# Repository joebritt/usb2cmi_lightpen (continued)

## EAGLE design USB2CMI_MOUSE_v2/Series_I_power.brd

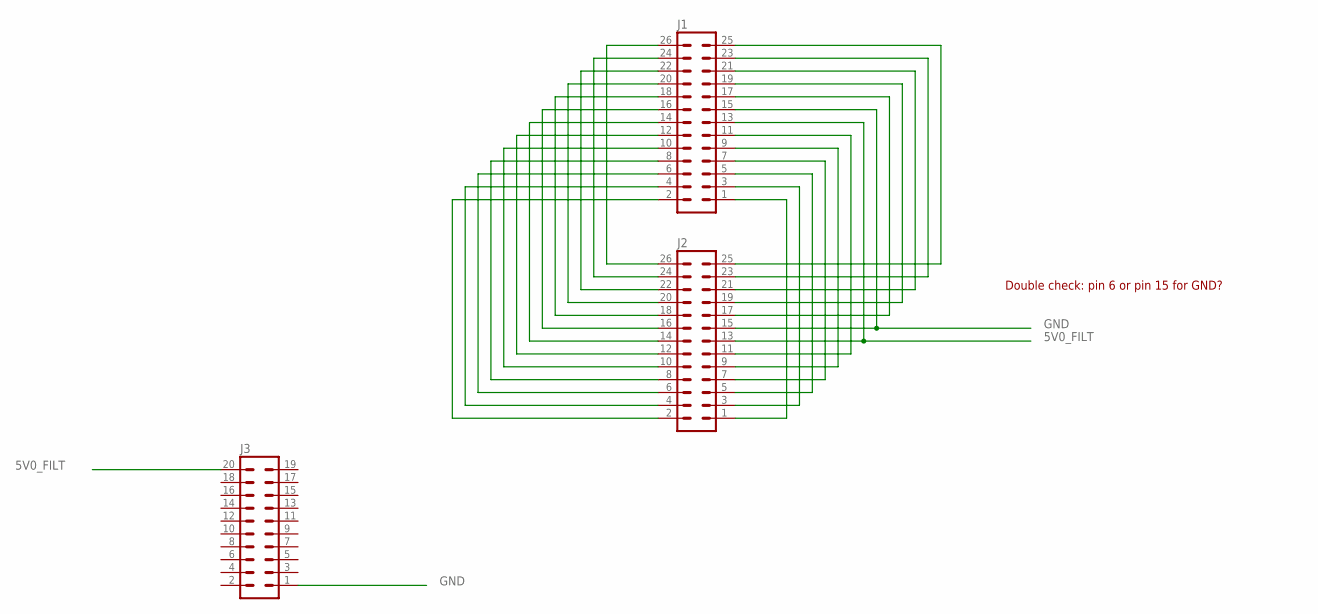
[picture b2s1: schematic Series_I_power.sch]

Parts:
J1, J2: 26H
J3: ML20

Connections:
5V0_FILT: J1.13, J2.13, J3.20
GND: J1.15, J2.15, J3.1
unnamed: J1.26, J2.26
unnamed: J1.24, J2.24
unnamed: J1.22, J2.22
unnamed: J1.20, J2.20
unnamed: J1.18, J2.18
unnamed: J1.16, J2.16
unnamed: J1.14, J2.14
unnamed: J1.12, J2.12
unnamed: J1.10, J2.10
unnamed: J1.8, J2.8
unnamed: J1.6, J2.6
unnamed: J1.4, J2.4
unnamed: J1.2, J2.2
unnamed: J1.1, J2.1
unnamed: J1.3, J2.3
unnamed: J1.5, J2.5
unnamed: J1.7, J2.7
unnamed: J1.9, J2.9
unnamed: J1.11, J2.11
unnamed: J1.17, J2.17
unnamed: J1.19, J2.19
unnamed: J1.21, J2.21
unnamed: J1.23, J2.23
unnamed: J1.25, J2.25

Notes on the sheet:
Double check: pin 6 or pin 15 for GND?

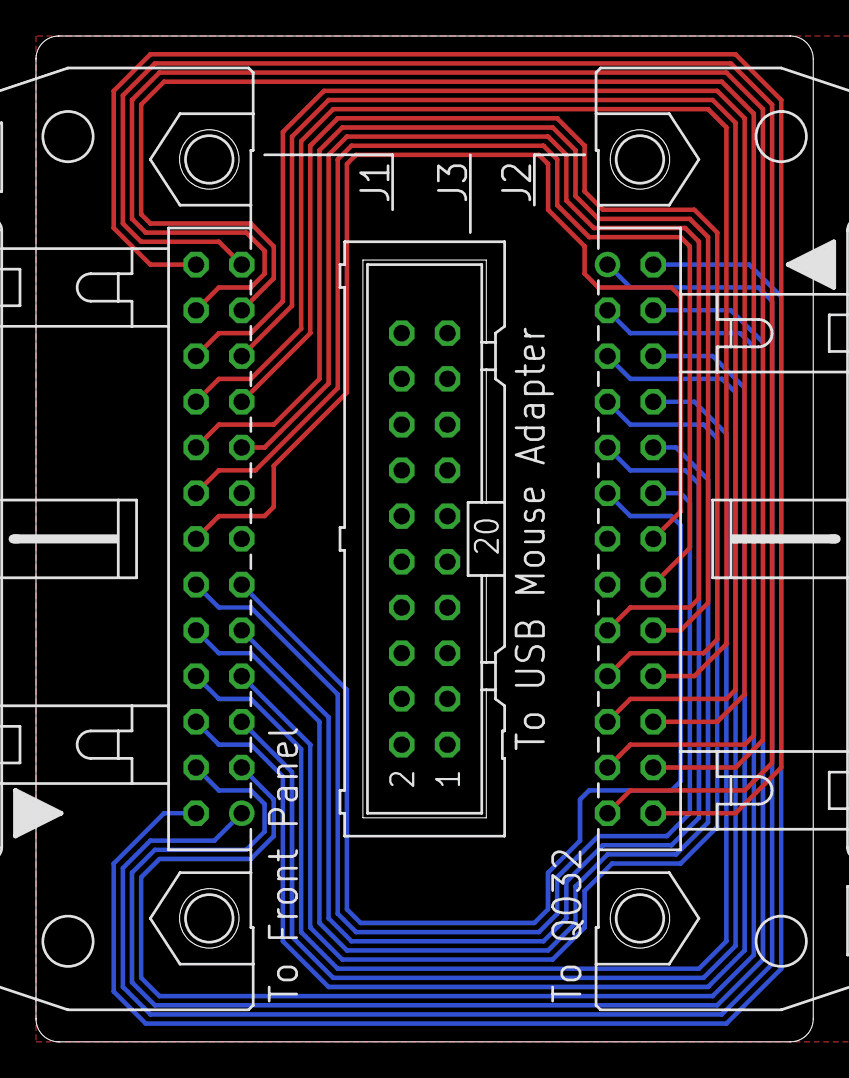
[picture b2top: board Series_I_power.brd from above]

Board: 2 copper layers, 43.2 x 55.9 mm, 3 parts (0 on the bottom side), 26 nets.

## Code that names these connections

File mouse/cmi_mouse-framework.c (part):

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	// Yellow (bottom) LED on RB1
	// Green (top) LED on RB0

	TRISBbits.TRISB1 = 0;	// RB1 is OUTPUT
	TRISBbits.TRISB0 = 0;	// RB0 is OUTPUT

	PORTBSET = 0x0002;		// Yellow LED off until we find the mouse

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	// TOUCH in from real LP is on RF1
	// !TOUCH out on RF0

	TRISFbits.TRISF1 = 1;	// RF1 is INPUT
	TRISFbits.TRISF0 = 0;	// RF0 is OUTPUT
	
	PORTFCLR = 0x0001;		// drive LOW (inactive, inverted)

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
	// HIT in from real LP is on RD0

	TRISDbits.TRISD0 = 1;	// RD0 is INPUT

	IEC0bits.INT0IE = 0;	// disable INT0
	INTCONbits.INT0EP = 0;	// RD0 is INT0, interrupt on falling edge
	IFS0bits.INT0IF = 0; 	// clear the interrupt flag


	// Output Compare 2

	TRISDbits.TRISD1 = 0;	// OC2 is on RD1
	PORTDCLR = 0x0002;		// ensure initially driven low (inactive, inverted)


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
	// Set up Input Capture 3 (VSYNC) for Timer 2/3

	TRISDbits.TRISD10 = 1;	// IC3 is on RD10

	IC3CON = 0;				// disable everything
	IC3CON = 0;
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
	// Set up Input Capture 2 (HSYNC) for Timer 2/3

	TRISDbits.TRISD9 = 1;	// IC2 is on RD9

	IC2CON = 0;				// disable everything
	IC2CON = 0;
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int flap_count = 0;
int pos_history_index = 0;
unsigned int pos_history[16];		// last 16 IC2BUF counts
									// used to detect HSYNC flapping due to loss of video signal

#define FLAP_THRESHOLD	0x01000000	// determined empirically
#define	MAX_FLAP_COUNT	10			// assume this many in a row is a good indicator of flapping
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
	show_cursor = 1;			// cursor on by default

	show_cursor_gpad = 1;		// separate one for G-Pad, since video detector automatically
								//  turns the other one back on
	mouse_left_button = 0;

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	while(1)
	{
		if (blinker++ > 0x8000) {
			blinker = 0;				// as long as we're getting VSYNCs, the VSYNC int
			PORTBINV = 0x0001;			//  handler will keep yanking blinker back to 0

			// If vsyncs (video) has been gone long enough to flip the LED, 
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
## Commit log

2020-08-01 Add files via upload
    Bootloader for the Fairlight CMI lightpen/USB mouse, built using Microchip MPLAB v8.63
    The interface uses a PIC32 microcontroller. The PIC32 Flash memory is divided into 2 sections:
    1. Bootloader (this code)
    2. Application (lightpen emulator)
    At startup this code checks if a USB mass storage device is attached, and if it contains a firmware update file.
    If it does, the file is copied into Flash as the Application. The Bootloader then jumps to the Application code.
2020-08-01 Add files via upload
    Application for the Fairlight CMI lightpen/USB mouse, built using Microchip MPLAB v8.63
    The interface uses a PIC32 microcontroller. The PIC32 Flash memory is divided into 2 sections:
    1. Bootloader
    2. Application (this code)
    This code tracks the position of a connected USB mouse and converts that position into signals which emulate signals generated by a Fairlight CMI lightpen.
    These lightpens are rare and difficult to repair. With this interface, a modern USB mouse can be used to drive the Fairlight UI.
2020-08-01 Add files via upload
    Wiring diagram, connector and cabling info.
2020-08-01 Add files via upload
    Original Fairlight CMI lightpen / USB mouse interface PCB, designed with Eagle
    Original aluminum front panel, designed with Front Panel Designer (for Front Panel Express)
2020-08-01 Add files via upload
    Front Panel Express design file for aluminum front panel.
    This is for the original external box version.
2020-08-01 Add files via upload
    Spec for multi-coax cable used for 5-pin XLR cable between CMI mainframe and VDU (monitor)
2020-08-01 Add files via upload
    Version 2 of the Fairlight lightpen / USB mouse interface.
    This version mounts inside the CMI, in an unused mainframe slot.
    +5V power is taken from the ribbon cable to the front panel.
    For a Series I or II, the "Series_I_power" board is needed, because the ribbon cable from the front panel has a different number of pins.
    2 lasercut "wings" are used to hold the board in place in the mainframe slot.
    A rear plate mounts to the bottom pan of the CMI, over 4 of the 8 I/O openings. You can lasercut this plate or use the .fpd file to order a cool aluminum one from Front Panel Express.
2020-08-01 Add files via upload
    Photos of the Version 1 (external box) and Version 2 (internal card) lightpen / USB mouse interfaces.
2020-08-01 Add files via upload
    Corrected error in one comment.
2020-08-01 Create README.md
    Added info about specific Microchip toolchain used to build.
2020-08-01 Add files via upload
    Pre-built images of the 2 needed hexfiles.
    Use the Microchip tools to flash bootloader.hex into the PIC32.
    Put cmimouse.hex on a USB thumbdrive (formatted with a DOS/FAT filesystem).
    Plug the thumbdrive into the interface USB port and power up the board.
    You should see the leds blink back and forth, then the cmimouse.hex file will be copied from the thumbdrive to the PIC32 flash.
    You'll see the LEDs change their flashing pattern when the code is flashed and started.
2020-08-02 Delete cmi_mouse_excellon.cam
    holdover from old version of board.
2020-08-02 Delete cmi_mouse_gerb274x.cam
    Holdover from old version of board.
2023-01-05 Update README.md
    Added link to OSHPark for PCB
2023-01-05 Add files via upload
    added PDFs of schematic and PCB.
2023-01-05 Update README.md
    added link to v1 PCB
2024-09-11 Added Front Panel Designer and DXF files for front panel
    Added Front Panel Designer and DXF files for front panel.
    I used Front Panel Designer to create the aluminum plate that the PCB mounts to, and used their service to manufacture it.
    I exported a DXF, which can be used to reproduce the panel with other tools.
2025-11-17 Add support for 2025/REV3 hardware.
    2025 version of the interface adds a switch to let the user select one of two cursor shapes:
    A: Classic 2010 Interface 3-line arrow cursor
    B: Large Crescent cursor, emulating cursor seen with the original lightpen
